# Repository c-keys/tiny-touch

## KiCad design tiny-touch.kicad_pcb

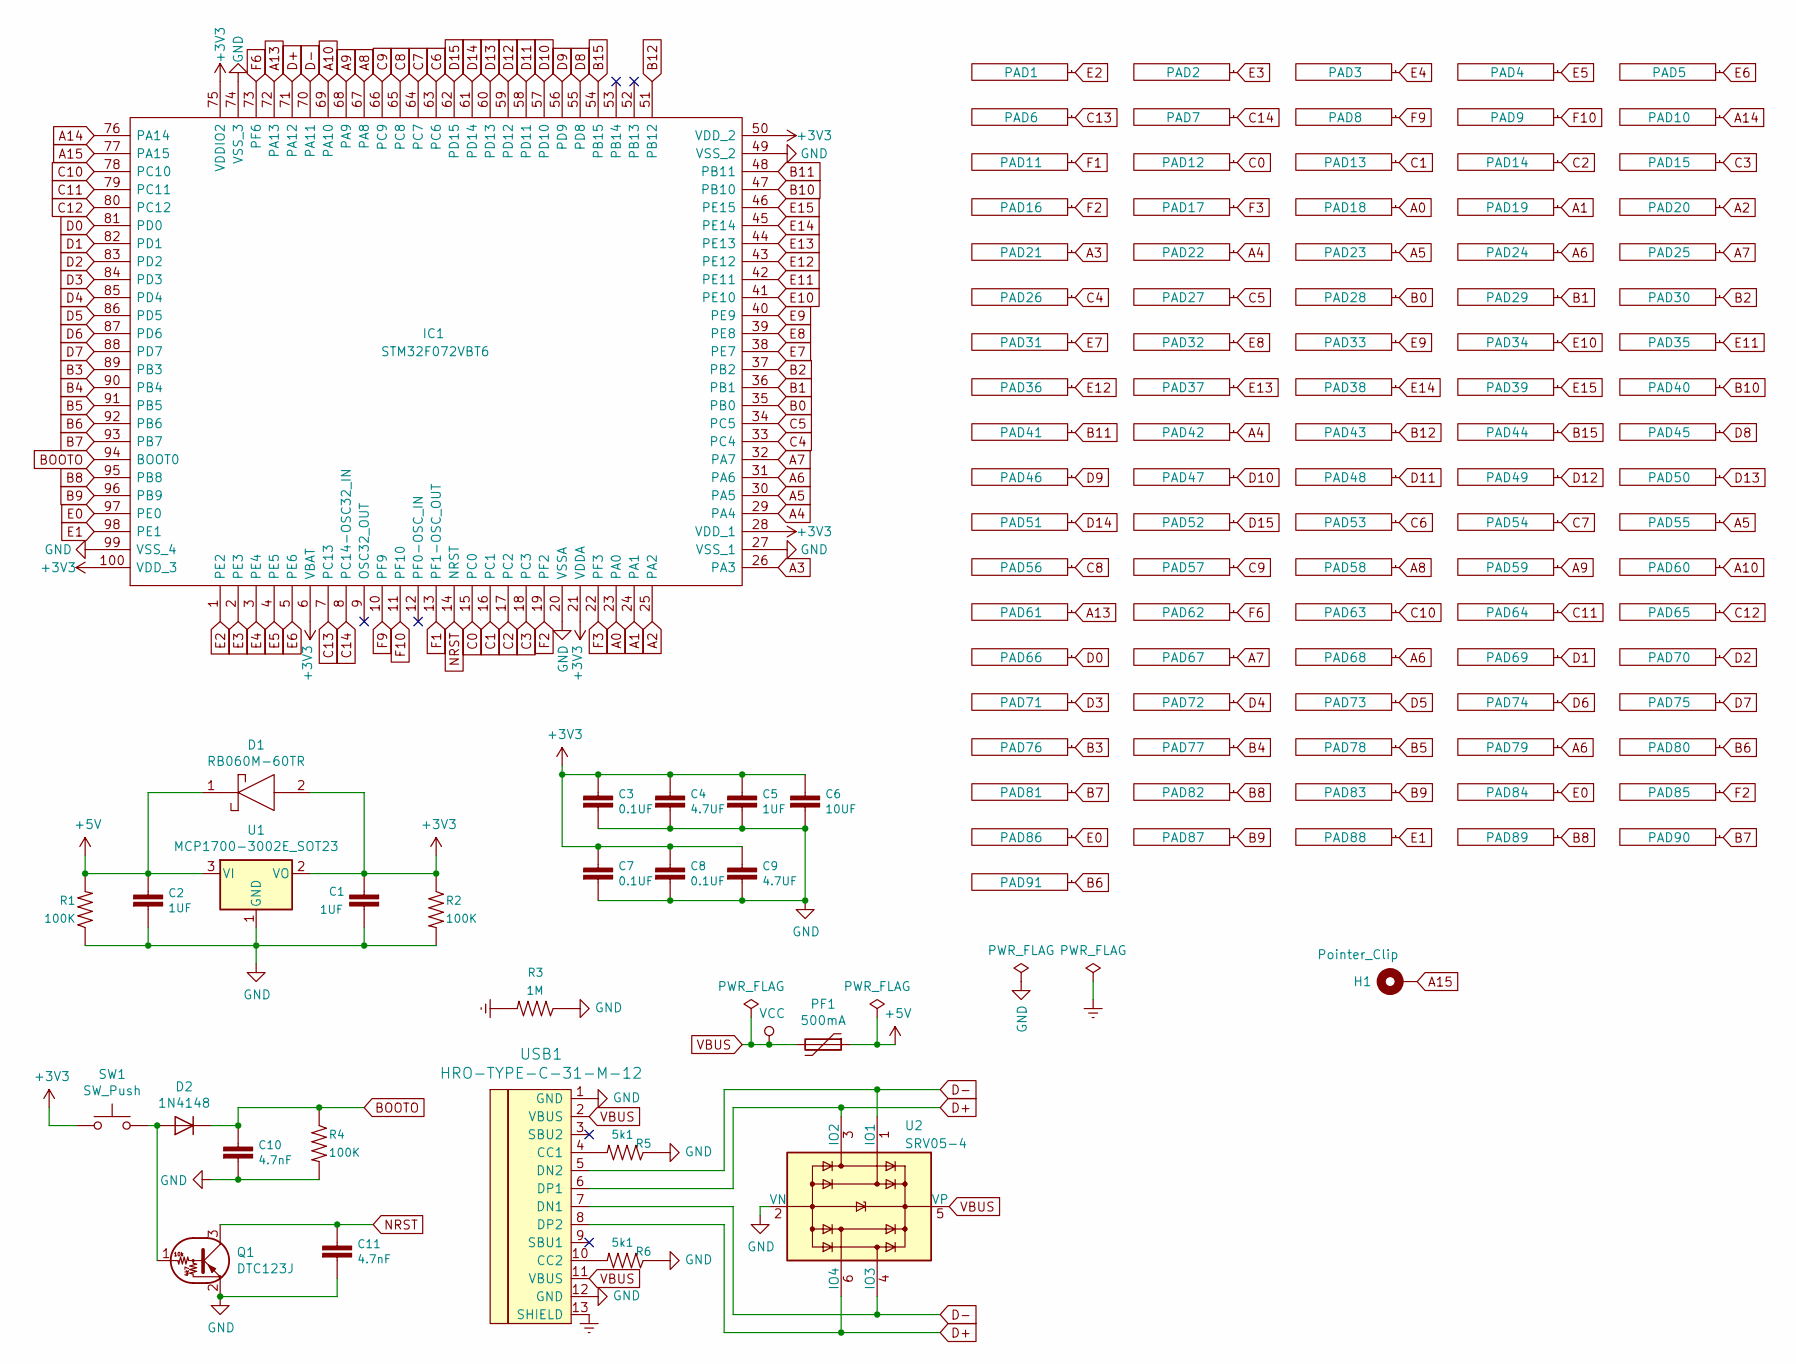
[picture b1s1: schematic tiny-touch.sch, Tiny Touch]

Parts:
C1, C2, C5: 1UF; C_0603_1608Metric_Pad1.05x0.95mm_HandSolder
C3, C7, C8: 0.1UF; C_0603_1608Metric_Pad1.05x0.95mm_HandSolder
C4, C9: 4.7UF; C_0603_1608Metric_Pad1.05x0.95mm_HandSolder
C6: 10UF; C_0603_1608Metric_Pad1.05x0.95mm_HandSolder
C10, C11: 4.7nF; C_0603_1608Metric_Pad1.05x0.95mm_HandSolder
D1: RB060M-60TR; PMDU; Manufacturer_Part_Number RB060M-60TR
D2: 1N4148; D_SOD-323_HandSoldering
H1: Pointer_Clip; microbit-clamp-hole-pad
IC1: STM32F072VBT6; QFP50P1600X1600X160-100N; Manufacturer_Part_Number STM32F072VBT6
PAD1, PAD2, PAD3, PAD4, PAD5, PAD6, PAD7, PAD8, PAD9, PAD10, PAD11, PAD12, PAD28, PAD29, PAD30, PAD31, PAD32, PAD33, PAD34, PAD35, PAD36, PAD37, PAD38, PAD39, PAD40, PAD41, PAD43, PAD44, PAD45, PAD46, PAD47, PAD48, PAD49, PAD50, PAD51, PAD52, PAD53, PAD56, PAD57, PAD58, PAD59, PAD60, PAD61, PAD62, PAD63, PAD64, PAD65, PAD66, PAD69, PAD70, PAD71, PAD72, PAD73, PAD74, PAD75, PAD76, PAD77, PAD78, PAD80, PAD81, PAD82, PAD83, PAD84, PAD86, PAD87, PAD88, PAD89, PAD90, PAD91: Tiny-Touch-Pad
PAD13, PAD14, PAD15, PAD21: Tiny-Touch-Pad; Tiny-Touch-Pad-2u
PAD16, PAD85: Tiny-Touch-Pad; Tiny-Touch-Pad-3u
PAD17, PAD18, PAD19, PAD20, PAD55, PAD79: Tiny-Touch-Pad; Tiny-Touch-Pad-1.75u
PAD22, PAD23, PAD42, PAD54: Tiny-Touch-Pad; Tiny-Touch-Pad-1.5u
PAD24, PAD25, PAD26, PAD27, PAD68: Tiny-Touch-Pad; Tiny-Touch-Pad-2.25u
PAD67: Tiny-Touch-Pad; Tiny-Touch-Pad-1.25u
PF1: 500mA; Fuse_1206_3216Metric_Pad1.42x1.75mm_HandSolder
Q1: DTC123J; SOT65P210X100-3N
R1, R2, R4: 100K; R_0603_1608Metric_Pad1.05x0.95mm_HandSolder
R3: 1M; R_0603_1608Metric_Pad1.05x0.95mm_HandSolder
R5, R6: 5k1; R_0603_1608Metric_Pad1.05x0.95mm_HandSolder
SW1: SW_Push; SW_Push_1P1T_NO_6x6mm_H9.5mm
U1: MCP1700-3002E_SOT23; SOT-23
U2: SRV05-4; SOT-23-6
USB1: HRO-TYPE-C-31-M-12; HRO-TYPE-C-31-M-12-HandSoldering

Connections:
+3V3: C1.2, C3.1, C4.1, C5.1, C6.1, C7.1, C8.1, C9.1, D1.2, IC1.6 (VBAT), IC1.21 (VDDA), IC1.28 (VDD_1), IC1.50 (VDD_2), IC1.75 (VDDIO2), IC1.100 (VDD_3), R2.1, SW1.1, U1.2 (VO)
+5V: C2.1, D1.1, PF1.1, R1.2, U1.3 (VI)
A0: IC1.23 (PA0), PAD18.1
A1: IC1.24 (PA1), PAD19.1
A2: IC1.25 (PA2), PAD20.1
A3: IC1.26 (PA3), PAD21.1
A4: IC1.29 (PA4), PAD22.1, PAD42.1
A5: IC1.30 (PA5), PAD23.1, PAD55.1
A6: IC1.31 (PA6), PAD24.1, PAD68.1, PAD79.1
A7: IC1.32 (PA7), PAD25.1, PAD67.1
A8: IC1.67 (PA8), PAD58.1
A9: IC1.68 (PA9), PAD59.1
A10: IC1.69 (PA10), PAD60.1
A13: IC1.72 (PA13), PAD61.1
A14: IC1.76 (PA14), PAD10.1
A15: H1.1, IC1.77 (PA15)
B0: IC1.35 (PB0), PAD28.1
B1: IC1.36 (PB1), PAD29.1
B2: IC1.37 (PB2), PAD30.1
B3: IC1.89 (PB3), PAD76.1
B4: IC1.90 (PB4), PAD77.1
B5: IC1.91 (PB5), PAD78.1
B6: IC1.92 (PB6), PAD80.1, PAD91.1
B7: IC1.93 (PB7), PAD81.1, PAD90.1
B8: IC1.95 (PB8), PAD82.1, PAD89.1
B9: IC1.96 (PB9), PAD83.1, PAD87.1
B10: IC1.47 (PB10), PAD40.1
B11: IC1.48 (PB11), PAD41.1
B12: IC1.51 (PB12), PAD43.1
B15: IC1.54 (PB15), PAD44.1
BOOTO: C10.1, D2.1 (K), IC1.94 (BOOT0), R4.1
C0: IC1.15 (PC0), PAD12.1
C1: IC1.16 (PC1), PAD13.1
C2: IC1.17 (PC2), PAD14.1
C3: IC1.18 (PC3), PAD15.1
C4: IC1.33 (PC4), PAD26.1
C5: IC1.34 (PC5), PAD27.1
C6: IC1.63 (PC6), PAD53.1
C7: IC1.64 (PC7), PAD54.1
C8: IC1.65 (PC8), PAD56.1
C9: IC1.66 (PC9), PAD57.1
C10: IC1.78 (PC10), PAD63.1
C11: IC1.79 (PC11), PAD64.1
C12: IC1.80 (PC12), PAD65.1
C13: IC1.7 (PC13), PAD6.1
C14: IC1.8 (PC14-OSC32_IN), PAD7.1
D0: IC1.81 (PD0), PAD66.1
D1: IC1.82 (PD1), PAD69.1
D2: IC1.83 (PD2), PAD70.1
D3: IC1.84 (PD3), PAD71.1
D4: IC1.85 (PD4), PAD72.1
D5: IC1.86 (PD5), PAD73.1
D6: IC1.87 (PD6), PAD74.1
D7: IC1.88 (PD7), PAD75.1
D8: IC1.55 (PD8), PAD45.1
D9: IC1.56 (PD9), PAD46.1
D10: IC1.57 (PD10), PAD47.1
D11: IC1.58 (PD11), PAD48.1
D12: IC1.59 (PD12), PAD49.1
D13: IC1.60 (PD13), PAD50.1
D14: IC1.61 (PD14), PAD51.1
D15: IC1.62 (PD15), PAD52.1
D+: IC1.71 (PA12), U2.3 (IO2), U2.6 (IO4), USB1.6 (DP1), USB1.8 (DP2)
D-: IC1.70 (PA11), U2.1 (IO1), U2.4 (IO3), USB1.5 (DN2), USB1.7 (DN1)
E0: IC1.97 (PE0), PAD84.1, PAD86.1
E1: IC1.98 (PE1), PAD88.1
E2: IC1.1 (PE2), PAD1.1
E3: IC1.2 (PE3), PAD2.1
E4: IC1.3 (PE4), PAD3.1
E5: IC1.4 (PE5), PAD4.1
E6: IC1.5 (PE6), PAD5.1
E7: IC1.38 (PE7), PAD31.1
E8: IC1.39 (PE8), PAD32.1
E9: IC1.40 (PE9), PAD33.1
E10: IC1.41 (PE10), PAD34.1
E11: IC1.42 (PE11), PAD35.1
E12: IC1.43 (PE12), PAD36.1
E13: IC1.44 (PE13), PAD37.1
E14: IC1.45 (PE14), PAD38.1
E15: IC1.46 (PE15), PAD39.1
F1: IC1.13 (PF1-OSC_OUT), PAD11.1
F2: IC1.19 (PF2), PAD16.1, PAD85.1
F3: IC1.22 (PF3), PAD17.1
F6: IC1.73 (PF6), PAD62.1
F9: IC1.10 (PF9), PAD8.1
F10: IC1.11 (PF10), PAD9.1
GND: C1.1, C2.2, C3.2, C4.2, C5.2, C6.2, C7.2, C8.2, C9.2, C10.2, C11.2, IC1.20 (VSSA), IC1.27 (VSS_1), IC1.49 (VSS_2), IC1.74 (VSS_3), IC1.99 (VSS_4), Q1.2 (E), R1.1, R2.2, R3.1, R4.2, R5.1, R6.1, U1.1 (GND), U2.2 (VN), USB1.1 (GND), USB1.12 (GND)
GNDREF: R3.2, USB1.13 (SHIELD)
NRST: C11.1, IC1.14 (NRST), Q1.3 (C)
unnamed: D2.2 (A), Q1.1 (B), SW1.2
unnamed: R5.2, USB1.4 (CC1)
unnamed: R6.2, USB1.10 (CC2)
VBUS: PF1.2, U2.5 (VP), USB1.2 (VBUS), USB1.11 (VBUS)

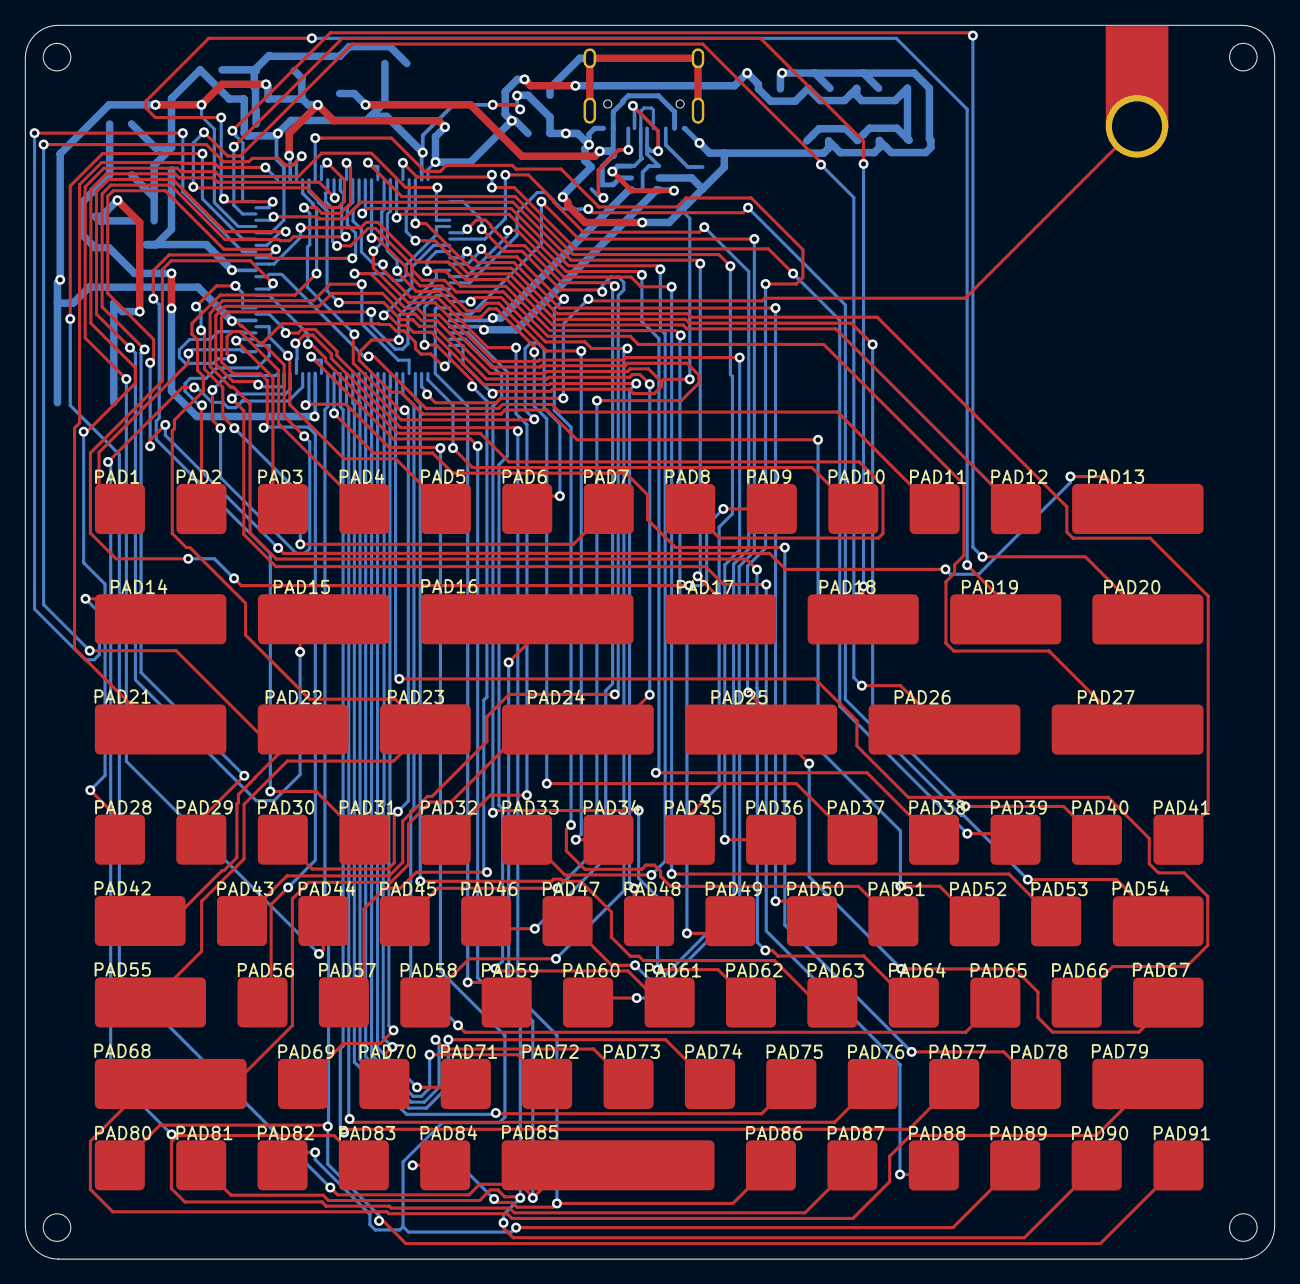
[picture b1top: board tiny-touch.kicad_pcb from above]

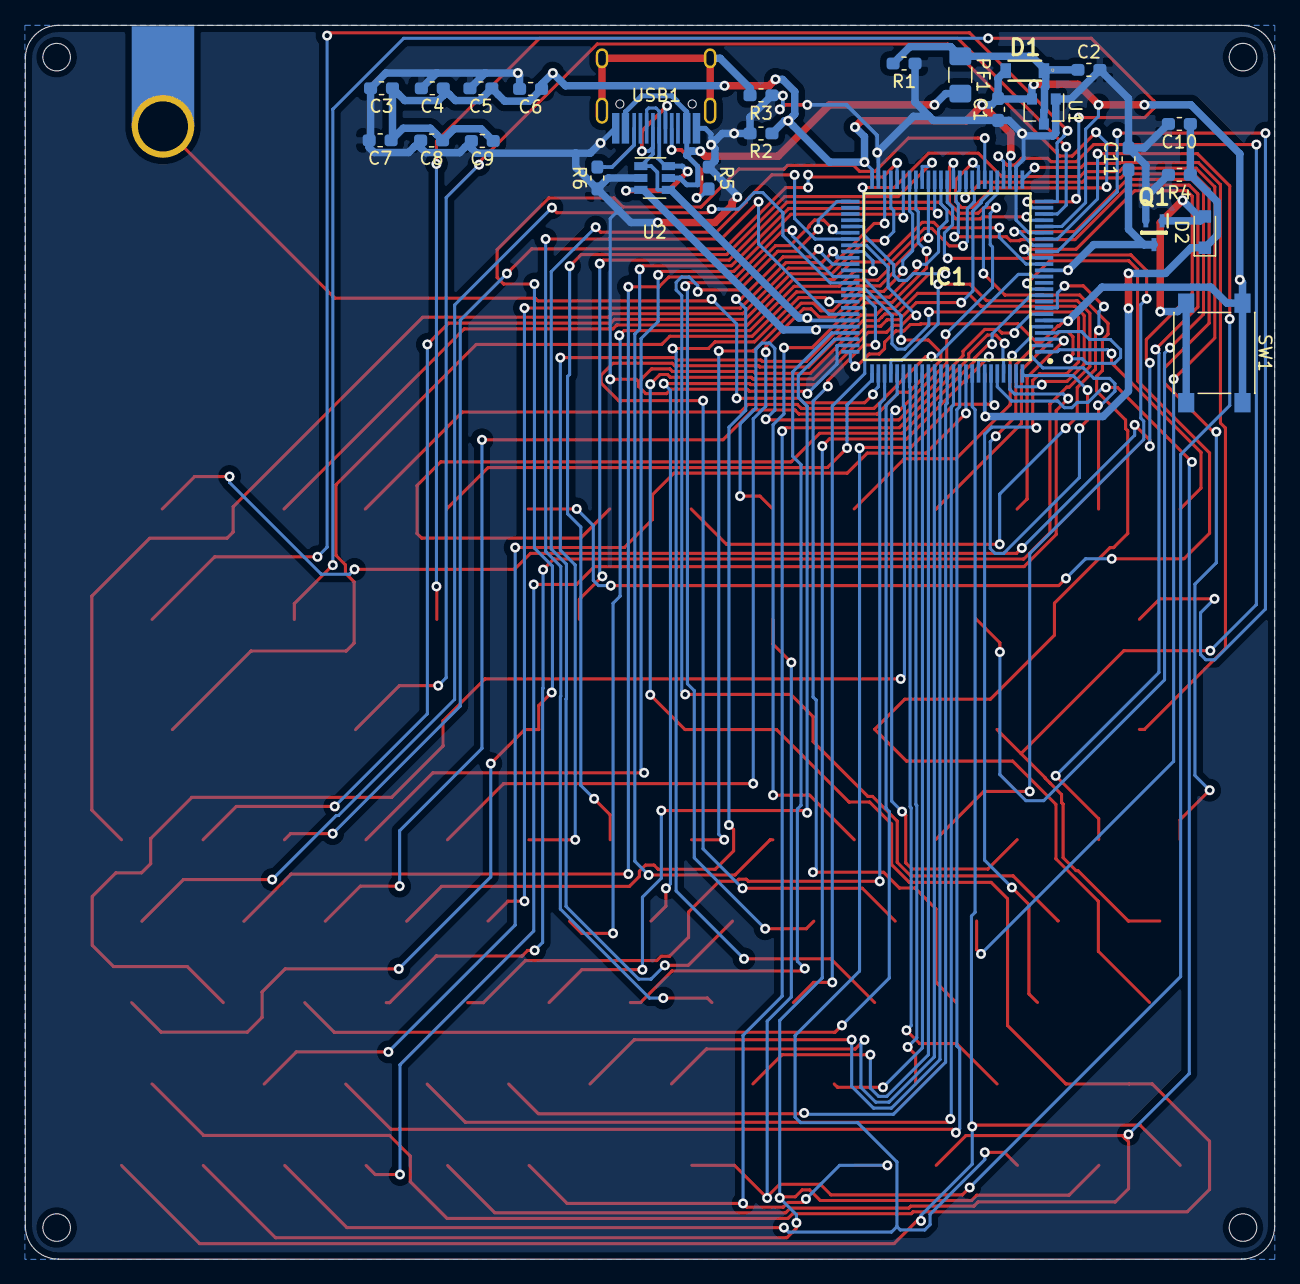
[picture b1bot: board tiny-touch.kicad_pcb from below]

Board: 2 copper layers, 99.8 x 98.5 mm, 122 parts (26 on the bottom side), 93 nets.

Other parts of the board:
HOLE1, HOLE1#2, HOLE1#3, HOLE1#4: MountingHole_2.2mm_M2

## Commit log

2020-07-12 Add USB C
2020-07-13 Re-organize schematic
2020-07-13 Label all pins on chip
2020-07-13 Add and label key pads
2020-07-14 Assign all switches to pins
2020-07-14 Begin PCB layout
2020-07-15 Fix footprint size/spacing
2020-07-15 Complete layout of keys
2020-07-15 Rename all switches on PCB
2020-07-18 Start running traces
2020-07-20 Continue tracing
2020-07-21 Try to add more traces
2020-07-21 Undo renaming of references
2020-07-21 Flip components to back
2020-07-22 Simplify layout
2020-07-23 Route major power lines
2020-07-23 Back to 2 layer
2020-07-23 2-layer auto-routed with FreeRouting
2020-07-23 Fixed small issues and connected all pins
2020-07-23 Add all traces and gerbers for main board
